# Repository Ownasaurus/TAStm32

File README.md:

# TAStm32
Please see the "Projects" section for an overview of the current status of this project!

Please see the "Wiki" section for the technical details of the serial communication protocol!

### Overview

This project aims to create an easy-to-use, multi-system TAS replay device to be used on actual consoles. The name of this project comes from the fact that it is powered by a STM32F4 microcontroller.

## How to use this device

#### Get Python3!
Install the [latest Python 3 release](https://www.python.org/downloads/)

(You may need to log out/log in to refresh the PATH variable)

Then install the required python modules with the following command:

    python3 -m pip install -r python/requirements.txt
    
#### Linux users -- make sure you are in the dialout and plugdev groups!

### Get the python scripts

Download the latest python scripts from https://github.com/Ownasaurus/TAStm32/releases/download/latest/python.zip

### Usage

Dumped TAS movies are available in the [TASBot projects repo](https://github.com/dwangoac/TASBot-Projects/tree/master/replayfiles)

[Scripts to dump your own TASes](https://github.com/dwangoac/TASBot-Projects/blob/master/Dump_Scripts/)

Once you've prepared a movie dump, use it with the TAStm32. Here is one example example is here:

    python3 tastm32.py --console snes --players 1,5 --dpcm --clock 14 --transition 2123 A --blank 1 smb3_agdq.r16m
    
Another option is to use python to run main.py, allowing you to utilize a GUI crated by Zayitskin. You can find more information on his repo here: https://github.com/Zayitskin/TAStm32GUI

## Upgrading firmware 

If it's the first time you're flashing it, short the "DFU" Pins (J13) while plugging tastm32 in.

#### Linux
    apt install dfu-util
OR the equivalent in your distribution. Then run:

    make v3 && make flash

Or :

    make v4 && make flash

#### Windows
1. Install STM32CubeProgrammer
1. Run the tastm32-dfu.py script to put the device in DFU mode (or if it's the first time you're flashing it, short the "DFU" Pins (J13) while plugging tastm32's USB cable into your computer).
1. Use the STM32CubeProgrammer software to flash the latest firmware. The latest firmware can always be found here: https://github.com/Ownasaurus/TAStm32/releases/download/latest/tastm32v3.hex
or
https://github.com/Ownasaurus/TAStm32/releases/download/latest/tastm32v4.hex

## Development (advanced users)

Do you want to fork the codebase and make your own tweaks? Here is some information that may help you.

### Compilation

#### Linux
    apt install gcc-arm-none-eabi binutils-arm-none-eabi libnewlib-arm-none-eabi
OR the equivalent in your distribution. Then run:

    make v3
    
Or : 

    make v4
    
Depending on if you have a v3 or v4 board. (v4 boards were released after July 2021)

#### Windows
1. Install Atollic TrueStudio
1. Right-click on the project > Build Configurations > Set Active, then click "Release v3" or "Release v4" depending on your board version. (v4s came out around July 2021)
1. Project > Build Project and check that the console shows no errors. The last line before "build finished" should be "arm-atollic-eabi-objcopy -O ihex TAStm32.elf TAStm32.hex".
1. Feel free to use the helper scripts "setenv.bat" and either "flashv3.bat" or "flashv4.bat" to assist in flashing firmware. These scripts will work if you have compiled using TrueStudio and if you have STM32CubeProgrammer installed.

### Special Thanks
#### rasteri (@rasteri) - Standalone USB playback, SNES multitap, v4 PCB, and more!
#### TheMas3212 (@TheMas3212) - Aided with all things python, designing the serial communication protocol, helping with PCB design, and debugging throughout the whole process.
#### total (@tewtal) - Helped with NES/SNES protocol and debugging. Provided his code as a reference
#### booto (@booto) - Helped fix N64/GC protocols, serial-over-USB, and debugging
#### Skippy - Pretty much helped a little bit with everything: including software, hardware, advice on proper tools, and more!

dwangoAC (@dwangoac) - warmly accepting me into the TASBot community

micro500 (@micro500) - spent a lot of time teaching me how console replay devices work at a low level

true - for teaching me hardware concepts, helping me choose the perfect MCU for the job, and explaining a lot of low-level things to me

Tien Majerle (@MaJerle) - the owner of https://stm32f4-discovery.net/ helped me with the function which jumps to the DFU bootloader code

CraftedCart - Designed the awesome-looking 3D case

Ilari - for being an extraordinary wealth of knowledge on most topics

Serisium (@serisium) - helped with debugging and PCB design

rcombs (@rcombs) - helped with optimizing the N64 protocol

Sauraen (@sauraen) - Linux setup and installation notes, multiplayer GC/N64 support, misc. GC/N64 improvements

Derf - worked on debugging the genesis protocol together

sspx (@SuperSpyTX) - For help with finding a bug in the N64 controller identity code.

#### If I accidentally forgot to credit you, please let me know so I can fix it!

 - Ownasaurus

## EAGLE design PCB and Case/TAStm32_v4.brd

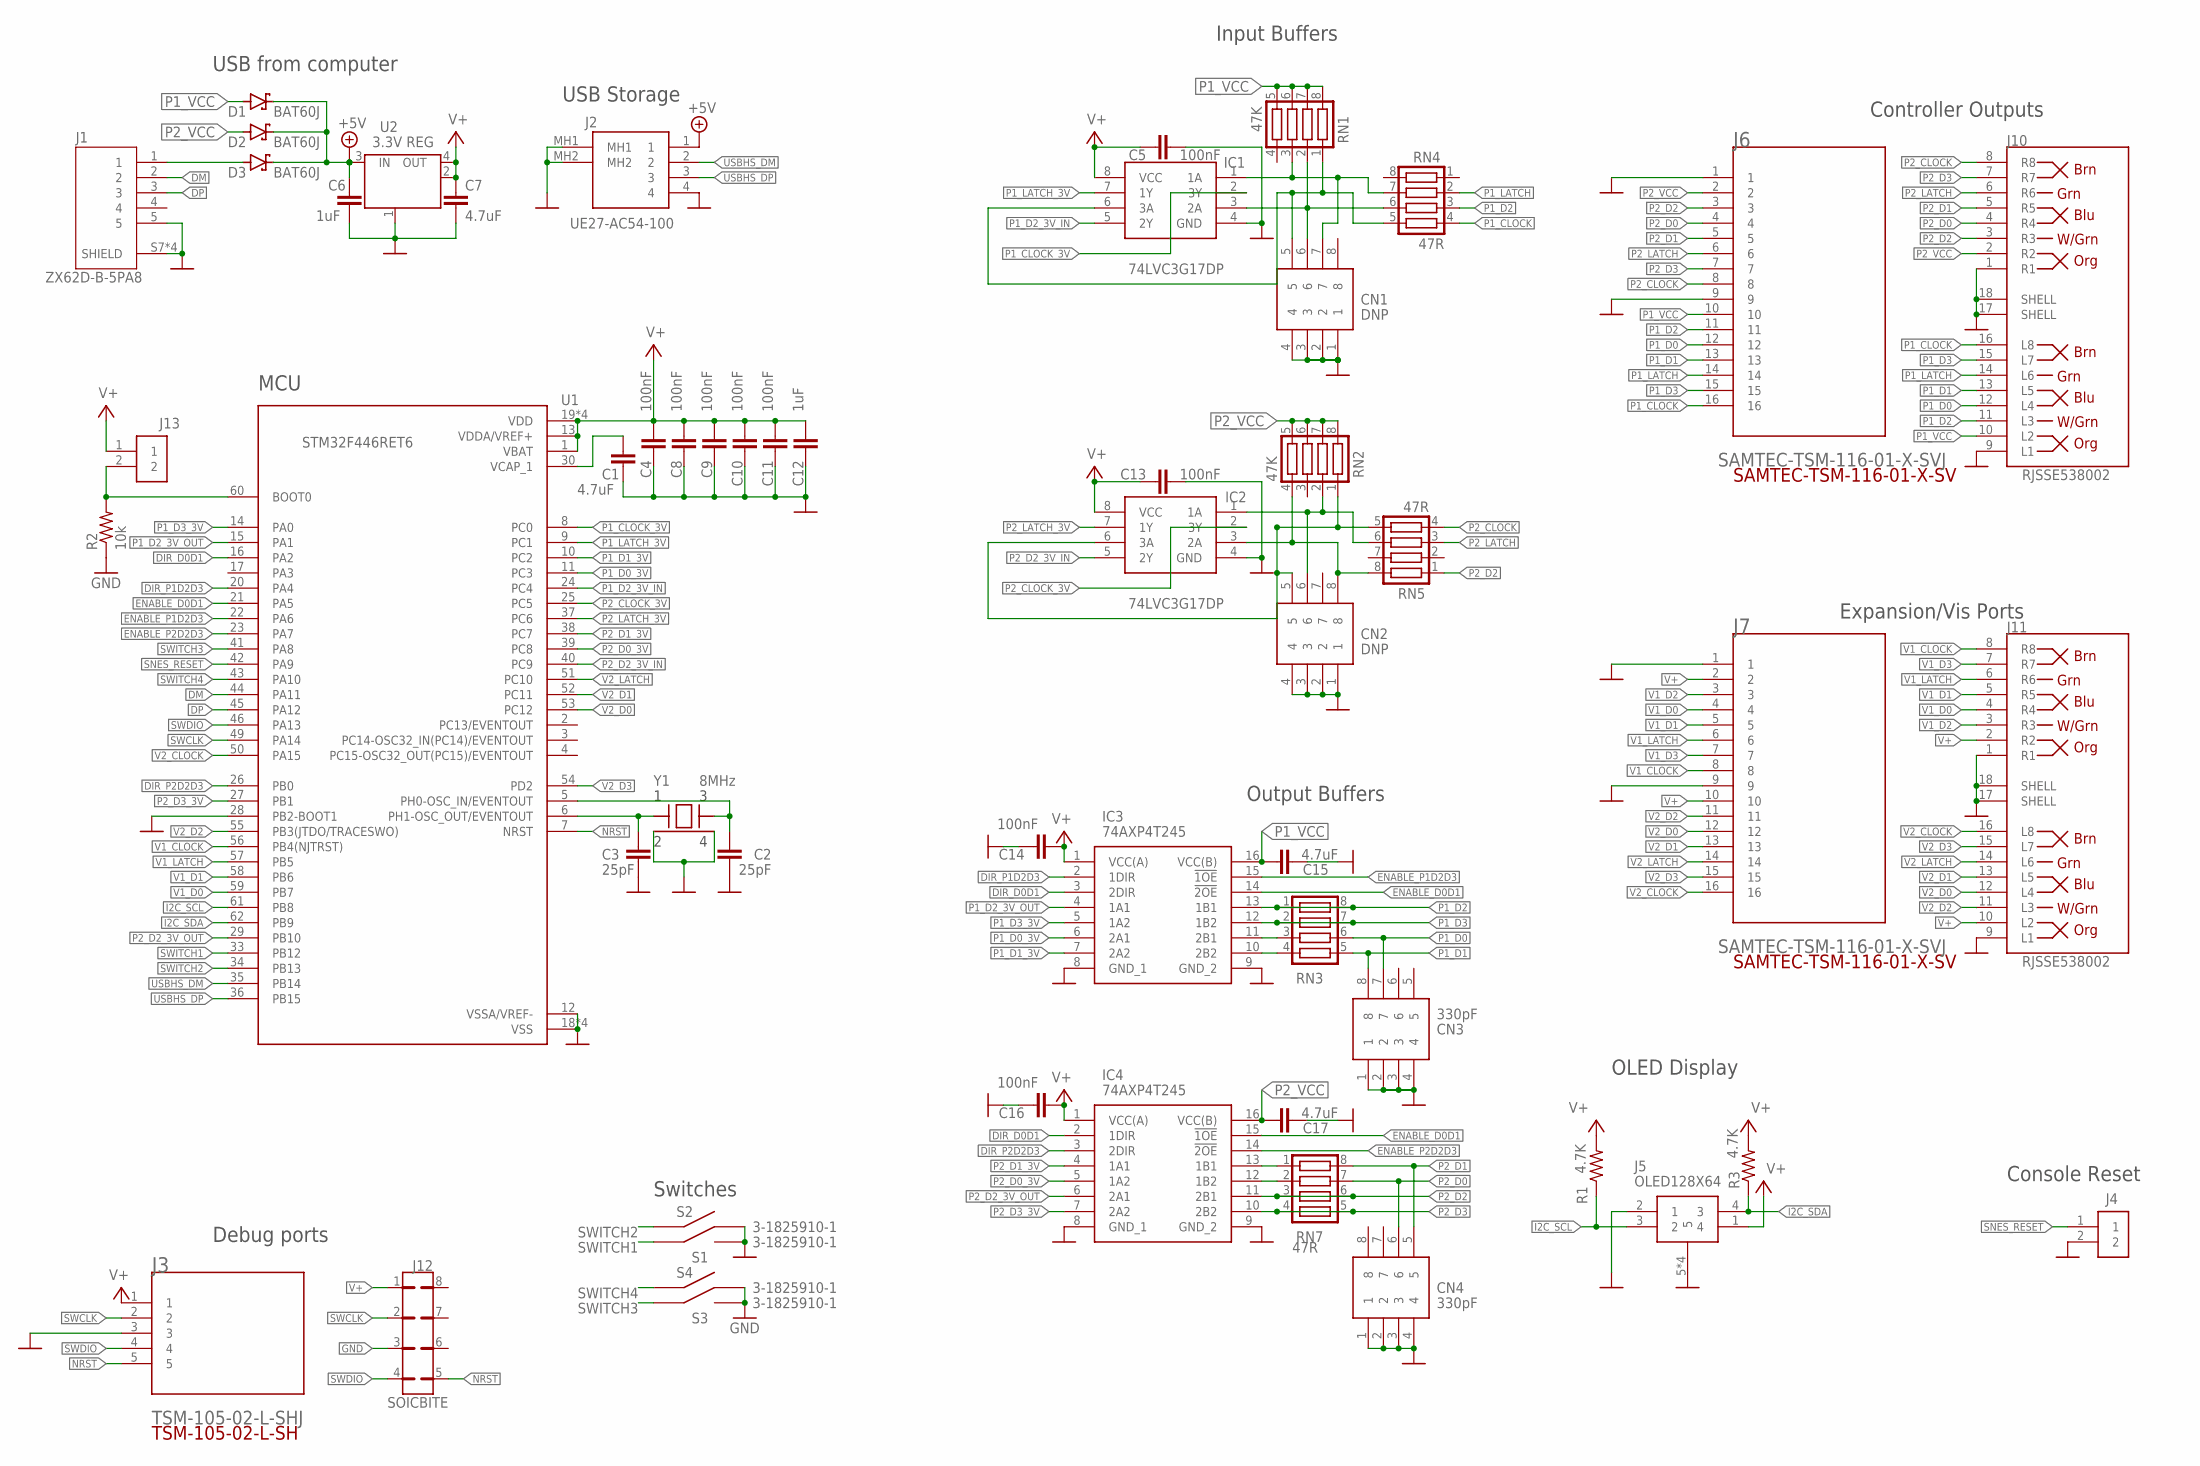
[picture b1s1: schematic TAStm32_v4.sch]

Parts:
C1, C7, C15, C17: 4.7uF; C0603K
C2, C3: 25pF; C0603K
C4, C5, C8, C9, C10, C11, C13, C14, C16: 100nF; C0603K
C6, C12: 1uF; C0603K
CN1, CN2: DNP; CA0612KRX7R7BB104
CN3, CN4: 330pF; CA0612KRX7R7BB104
D1, D2, D3: BAT60J; DIODE_SOD323_ST
IC1, IC2: 74LVC3G17DP; SOP65P400X110-8N
IC3, IC4: 74AXP4T245; SOP65P640X110-16N
J1: ZX62D-B-5PA8; HIROSE_ZX62D-B-5PA8
J2: UE27-AC54-100; UE27AC54100
J3: TSM-105-02-L-SHJ; TSM-105-02-L-SH
J4, J13: CONSOLE_RESET; SAMTEC-TSM-102-01-X-SH
J5: OLED128X64; OLED
J6, J7: SAMTEC-TSM-116-01-X-SVJ; SAMTEC-TSM-116-01-X-SV
J10, J11: RJSSE538002; AMPHENOL_RJSSE538002
J12: SOICBITE
R1, R3: 4.7K; R0805
R2: 10k; R0805
RN1, RN2: 47K; CTS742C083
RN3: CTS742C083
RN4, RN5, RN7: 47R; CTS742C083
S1, S2, S3, S4: 3-1825910-1; 3-1825910-1_318259101
U1: STM32F446RET6; QFP50P1200X1200X160-64N
U2: 3.3V REG; SOT223
Y1: 8MHz; DFN-4

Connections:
+5V: C6.2, D1.C, D2.C, D3.C, J2.1, U2.3 (IN)
BOOT0: J13.2, R2.2, U1.60 (BOOT0)
DIR_D0D1: IC3.3 (2DIR), IC4.2 (1DIR), U1.16 (PA2)
DIR_P1D2D3: IC3.2 (1DIR), U1.20 (PA4)
DIR_P2D2D3: IC4.3 (2DIR), U1.26 (PB0)
DM: J1.2, U1.44 (PA11)
DP: J1.3, U1.45 (PA12)
ENABLE_D0D1: IC3.14 (!2OE), IC4.15 (!1OE), U1.21 (PA5)
ENABLE_P1D2D3: IC3.15 (!1OE), U1.22 (PA6)
ENABLE_P2D2D3: IC4.14 (!2OE), U1.23 (PA7)
GND: C1.2, C2.1, C3.1, C4.1, C5.2, C6.1, C7.1, C8.1, C9.1, C10.1, C11.1, C12.1, C13.2, C14.1, C15.2, C16.1, C17.2, CN1.1, CN1.2, CN1.3, CN1.4, CN2.1, CN2.2, CN2.3, CN2.4, CN3.1, CN3.2, CN3.3, CN3.4, CN4.1, CN4.2, CN4.3, CN4.4, IC1.4 (GND), IC2.4 (GND), IC3.8 (GND_1), IC3.9 (GND_2), IC4.8 (GND_1), IC4.9 (GND_2), J1.5, J1.S7 (SHIELD), J1.S8 (SHIELD), J1.S9 (SHIELD), J1.S10 (SHIELD), J2.4, J2.MH1, J2.MH2, J3.3, J4.2, J5.2 (1), J5.5, J5.6 (5), J5.7 (5), J5.8 (5), J6.1, J6.9, J7.1, J7.9, J10.1 (R1), J10.9 (L1), J10.17 (SHELL), J10.18 (SHELL), J11.1 (R1), J11.9 (L1), J11.17 (SHELL), J11.18 (SHELL), J12.3, R2.1, S1.3, S1.4, S2.3, S2.4, S3.3, S3.4, S4.3, S4.4, U1.12 (VSSA/VREF-), U1.18 (VSS), U1.28 (PB2-BOOT1), U1.31 (VSS)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
I2C_SCL: J5.3 (2), R1.1, U1.61 (PB8)
I2C_SDA: J5.4 (3), R3.1, U1.62 (PB9)
unnamed: D3.A, J1.1
unnamed: CN2.6, IC2.1 (1A), RN2.2, RN5.6
unnamed: C3.2, U1.6 (PH1-OSC_OUT/EVENTOUT), Y1.1
unnamed: CN2.5, IC2.6 (3A), RN2.1, RN5.5
unnamed: CN2.8, IC2.3 (2A), RN2.4, RN5.8
unnamed: IC3.11 (2B1), RN3.3
unnamed: IC3.10 (2B2), RN3.4
unnamed: IC4.12 (1B2), RN7.2
unnamed: IC4.13 (1B1), RN7.1
unnamed: CN1.7, IC1.1 (1A), RN1.3, RN4.7
unnamed: CN1.5, IC1.6 (3A), RN1.1, RN4.5
unnamed: CN1.6, IC1.3 (2A), RN1.2, RN4.6
NRST: J3.5, J12.5, U1.7 (NRST)
P1_CLOCK: J6.16, J10.16 (L8), RN4.4
P1_CLOCK_3V: IC1.2 (3Y), U1.8 (PC0)
P1_D0: CN3.7, J6.12, J10.12 (L4), RN3.6
P1_D0_3V: IC3.6 (2A1), U1.11 (PC3)
P1_D1: CN3.8, J6.13, J10.13 (L5), RN3.5
P1_D1_3V: IC3.7 (2A2), U1.10 (PC2)
P1_D2: IC3.13 (1B1), J6.11, J10.11 (L3), RN3.1, RN3.8, RN4.3
P1_D2_3V_IN: IC1.5 (2Y), U1.24 (PC4)
P1_D2_3V_OUT: IC3.4 (1A1), U1.15 (PA1)
P1_D3: IC3.12 (1B2), J6.15, J10.15 (L7), RN3.2, RN3.7
P1_D3_3V: IC3.5 (1A2), U1.14 (PA0)
P1_LATCH: J6.14, J10.14 (L6), RN4.2
P1_LATCH_3V: IC1.7 (1Y), U1.9 (PC1)
P1_VCC: C15.1, D1.A, IC3.16 (VCC(B)), J6.10, J10.10 (L2), RN1.5, RN1.6, RN1.7, RN1.8
P2_CLOCK: J6.8, J10.8 (R8), RN5.4
P2_CLOCK_3V: IC2.2 (3Y), U1.25 (PC5)
P2_D0: CN4.6, J6.4, J10.4 (R4), RN7.7
P2_D0_3V: IC4.5 (1A2), U1.39 (PC8)
P2_D1: CN4.5, J6.5, J10.5 (R5), RN7.8
P2_D1_3V: IC4.4 (1A1), U1.38 (PC7)
P2_D2: IC4.11 (2B1), J6.3, J10.3 (R3), RN5.1, RN7.3, RN7.6
P2_D2_3V_IN: IC2.5 (2Y), U1.40 (PC9)
P2_D2_3V_OUT: IC4.6 (2A1), U1.29 (PB10)
P2_D3: IC4.10 (2B2), J6.7, J10.7 (R7), RN7.4, RN7.5
P2_D3_3V: IC4.7 (2A2), U1.27 (PB1)
P2_LATCH: J6.6, J10.6 (R6), RN5.3
P2_LATCH_3V: IC2.7 (1Y), U1.37 (PC6)
P2_VCC: C17.1, D2.A, IC4.16 (VCC(B)), J6.2, J10.2 (R2), RN2.5, RN2.6, RN2.7, RN2.8
SNES_RESET: J4.1, U1.42 (PA9)
SWCLK: J3.2, J12.2, U1.49 (PA14)
SWDIO: J3.4, J12.4, U1.46 (PA13)
SWITCH1: S1.1, S1.2, U1.33 (PB12)
SWITCH2: S2.1, S2.2, U1.34 (PB13)
SWITCH3: S3.1, S3.2, U1.41 (PA8)
SWITCH4: S4.1, S4.2, U1.43 (PA10)
USBHS_DM: J2.2, U1.35 (PB14)
USBHS_DP: J2.3, U1.36 (PB15)
V1_CLOCK: J7.8, J11.8 (R8), U1.56 (PB4(NJTRST))
V1_D0: J7.4, J11.4 (R4), U1.59 (PB7)
V1_D1: J7.5, J11.5 (R5), U1.58 (PB6)
V1_D2: J7.3, J11.3 (R3)
V1_D3: J7.7, J11.7 (R7)
V1_LATCH: J7.6, J11.6 (R6), U1.57 (PB5)
V2_CLOCK: J7.16, J11.16 (L8), U1.50 (PA15)
V2_D0: J7.12, J11.12 (L4), U1.53 (PC12)
V2_D1: J7.13, J11.13 (L5), U1.52 (PC11)
V2_D2: J7.11, J11.11 (L3), U1.55 (PB3(JTDO/TRACESWO))
V2_D3: J7.15, J11.15 (L7), U1.54 (PD2)
V2_LATCH: J7.14, J11.14 (L6), U1.51 (PC10)
V+: C4.2, C5.1, C7.2, C8.2, C9.2, C10.2, C11.2, C12.2, C13.1, C14.2, C16.2, IC1.8 (VCC), IC2.8 (VCC), IC3.1 (VCC(A)), IC4.1 (VCC(A)), J3.1, J5.1 (4), J7.2, J7.10, J11.2 (R2), J11.10 (L2), J12.1, J13.1, R1.2, R3.2, U1.1 (VBAT), U1.13 (VDDA/VREF+), U1.19 (VDD), U1.32 (VDD), U1.48 (VDD), U1.64 (VDD), U2.2 (OUT), U2.4 (OUT)
VCAP: C1.1, U1.30 (VCAP_1)
XTAL1: C2.2, U1.5 (PH0-OSC_IN/EVENTOUT), Y1.3

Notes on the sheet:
USB from computer
USB Storage
MCU
Debug ports
OLED Display
Console Reset
Controller Outputs
Expansion/Vis Ports
Input Buffers
Output Buffers
Switches

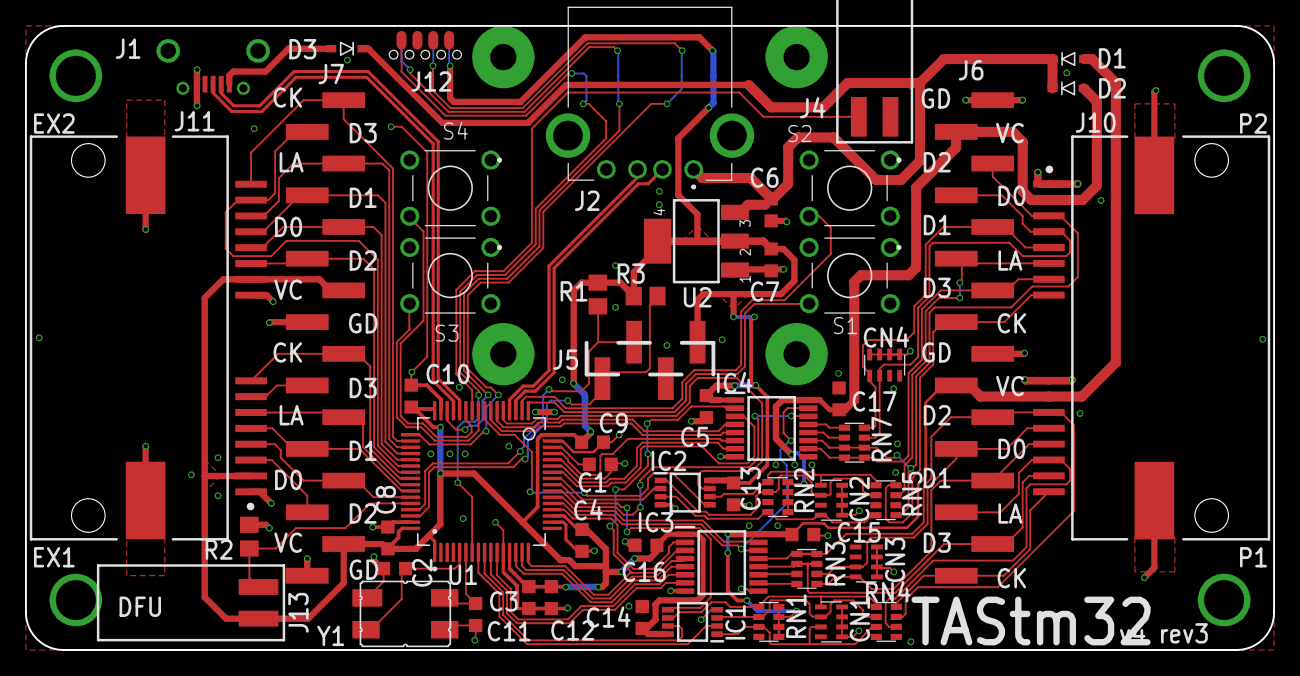
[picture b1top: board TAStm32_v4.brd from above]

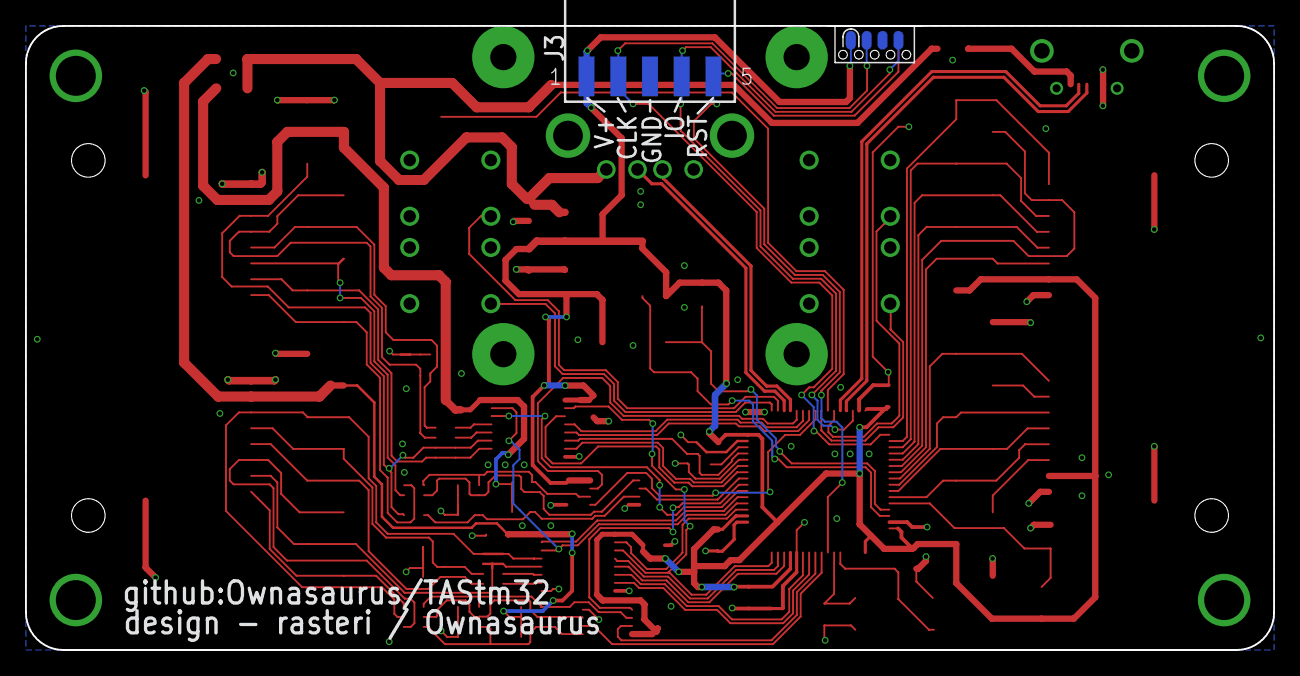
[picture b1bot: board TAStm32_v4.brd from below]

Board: 2 copper layers, 100.0 x 50.0 mm, 55 parts (2 on the bottom side), 78 nets.

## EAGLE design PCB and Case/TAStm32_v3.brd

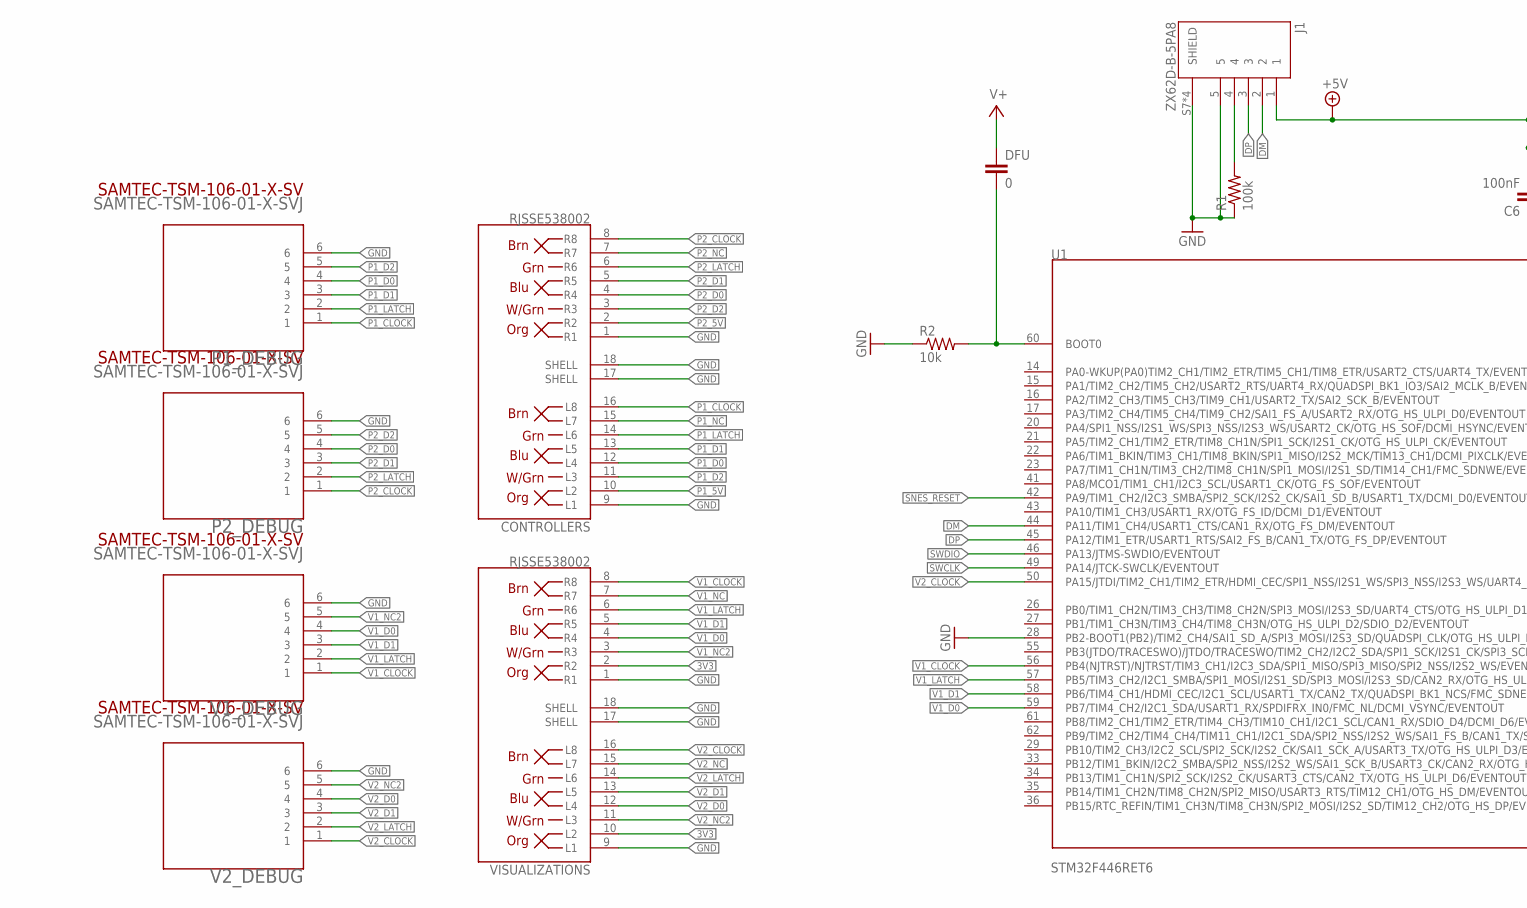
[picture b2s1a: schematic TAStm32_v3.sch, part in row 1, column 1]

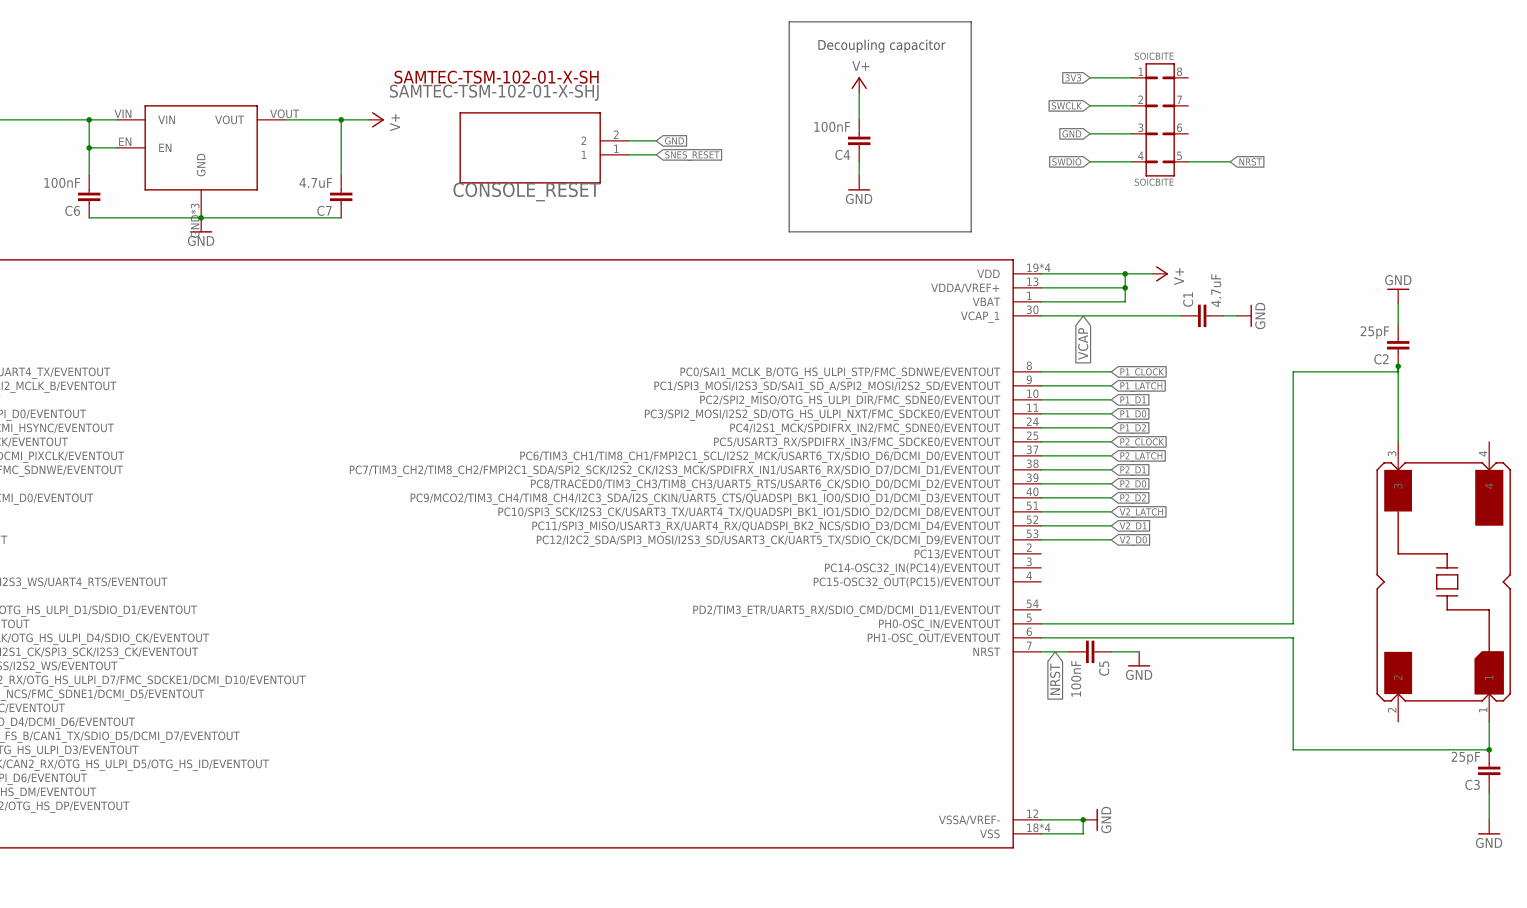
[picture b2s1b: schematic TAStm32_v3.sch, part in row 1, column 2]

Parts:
C1, C7: 4.7uF; C0805K
C2, C3: 25pF; C0805K
C4, C5, C6: 100nF; C0805K
CONSOLE_RESET: SAMTEC-TSM-102-01-X-SHJ; SAMTEC-TSM-102-01-X-SH
CONTROLLERS: RJSSE538002; AMPHENOL_RJSSE538002
DFU: 0; C0603
J1: ZX62D-B-5PA8; HIROSE_ZX62D-B-5PA8
P1_DEBUG, P2_DEBUG: SAMTEC-TSM-106-01-X-SVJ; SAMTEC-TSM-106-01-X-SV
R1: 100k; R0805
R2: 10k; R0805
SOICBITE: SOICBITE
U1: STM32F446RET6; QFP50P1200X1200X160-64N
V1_DEBUG, V2_DEBUG: SAMTEC-TSM-106-01-X-SVJ; SAMTEC-TSM-106-01-X-SV
VISUALIZATIONS: RJSSE538002; AMPHENOL_RJSSE538002
V_REG: S-1172B33-U5T1G
XTAL: ABMM-8.000MHZ-B2-T; DFN-4

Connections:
3V3: C4.2, C7.2, DFU.1, SOICBITE.1, U1.1 (VBAT), U1.13 (VDDA/VREF+), U1.19 (VDD), U1.32 (VDD), U1.48 (VDD), U1.64 (VDD), VISUALIZATIONS.2 (R2), VISUALIZATIONS.10 (L2), V_REG.VOUT
+5V: C6.2, J1.1, V_REG.EN, V_REG.VIN
BOOT0: DFU.2, R2.2, U1.60 (BOOT0)
DM: J1.2, U1.44 (PA11/TIM1_CH4/USART1_CTS/CAN1_RX/OTG_FS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)
DP: J1.3, U1.45 (PA12/TIM1_ETR/USART1_RTS/SAI2_FS_B/CAN1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)
GND: C1.2, C2.2, C3.1, C4.1, C5.1, C6.1, C7.1, CONSOLE_RESET.2, CONTROLLERS.1 (R1), CONTROLLERS.9 (L1), CONTROLLERS.17 (SHELL), CONTROLLERS.18 (SHELL), J1.5, J1.S7 (SHIELD), J1.S8 (SHIELD), J1.S9 (SHIELD), J1.S10 (SHIELD), P1_DEBUG.6, P2_DEBUG.6, R1.1, R2.1, SOICBITE.3, U1.12 (VSSA/VREF-), U1.18 (VSS), U1.28 (PB2-BOOT1(PB2)/TIM2_CH4/SAI1_SD_A/SPI3_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), U1.31 (VSS), U1.47 (VSS), U1.63 (VSS), V1_DEBUG.6, V2_DEBUG.6, VISUALIZATIONS.1 (R1), VISUALIZATIONS.9 (L1), VISUALIZATIONS.17 (SHELL), VISUALIZATIONS.18 (SHELL), V_REG.GND, V_REG.GND2 (GND), V_REG.GND3 (GND)
ID: J1.4, R1.2
NRST: C5.2, SOICBITE.5, U1.7 (NRST)
P1_5V: CONTROLLERS.10 (L2)
P1_CLOCK: CONTROLLERS.16 (L8), P1_DEBUG.1, U1.8 (PC0/SAI1_MCLK_B/OTG_HS_ULPI_STP/FMC_SDN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)
P1_D0: CONTROLLERS.12 (L4), P1_DEBUG.4, U1.11 (PC3/SPI2_MOSI/I2S2_SD/OTG_HS_ULPI_NXT/F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)
P1_D1: CONTROLLERS.13 (L5), P1_DEBUG.3, U1.10 (PC2/SPI2_MISO/OTG_HS_ULPI_DIR/FMC_SDNE0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)
P1_D2: CONTROLLERS.11 (L3), P1_DEBUG.5, U1.24 (PC4/I2S1_MCK/SPDIFRX_IN2/FMC_SDNE0/EVEN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)
P1_LATCH: CONTROLLERS.14 (L6), P1_DEBUG.2, U1.9 (PC1/SPI3_MOSI/I2S3_SD/SAI1_SD_A/SPI2_MO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)
P1_NC: CONTROLLERS.15 (L7)
P2_5V: CONTROLLERS.2 (R2)
P2_CLOCK: CONTROLLERS.8 (R8), P2_DEBUG.1, U1.25 (PC5/USART3_RX/SPDIFRX_IN3/FMC_SDCKE0/EV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)
P2_D0: CONTROLLERS.4 (R4), P2_DEBUG.4, U1.39 (PC8/TRACED0/TIM3_CH3/TIM8_CH3/UART5_RTS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)
P2_D1: CONTROLLERS.5 (R5), P2_DEBUG.3, U1.38 (PC7/TIM3_CH2/TIM8_CH2/FMPI2C1_SDA/SPI2_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)
P2_D2: CONTROLLERS.3 (R3), P2_DEBUG.5, U1.40 (PC9/MCO2/TIM3_CH4/TIM8_CH4/I2C3_SDA/I2S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)
P2_LATCH: CONTROLLERS.6 (R6), P2_DEBUG.2, U1.37 (PC6/TIM3_CH1/TIM8_CH1/FMPI2C1_SCL/I2S2_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)
P2_NC: CONTROLLERS.7 (R7)
SNES_RESET: CONSOLE_RESET.1, U1.42 (PA9/TIM1_CH2/I2C3_SMBA/SPI2_SCK/I2S2_CK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)
SWCLK: SOICBITE.2, U1.49 (PA14/JTCK-SWCLK/EVENTOUT)
SWDIO: SOICBITE.4, U1.46 (PA13/JTMS-SWDIO/EVENTOUT)
V1_CLOCK: U1.56 (PB4(NJTRST)/NJTRST/TIM3_CH1/I2C3_SDA/SP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), V1_DEBUG.1, VISUALIZATIONS.8 (R8)
V1_D0: U1.59 (PB7/TIM4_CH2/I2C1_SDA/USART1_RX/SPDIFRX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), V1_DEBUG.4, VISUALIZATIONS.4 (R4)
V1_D1: U1.58 (PB6/TIM4_CH1/HDMI_CEC/I2C1_SCL/USART1_T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), V1_DEBUG.3, VISUALIZATIONS.5 (R5)
V1_LATCH: U1.57 (PB5/TIM3_CH2/I2C1_SMBA/SPI1_MOSI/I2S1_S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), V1_DEBUG.2, VISUALIZATIONS.6 (R6)
V1_NC: VISUALIZATIONS.7 (R7)
V1_NC2: V1_DEBUG.5, VISUALIZATIONS.3 (R3)
V2_CLOCK: U1.50 (PA15/JTDI/TIM2_CH1/TIM2_ETR/HDMI_CEC/SP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), V2_DEBUG.1, VISUALIZATIONS.16 (L8)
V2_D0: U1.53 (PC12/I2C2_SDA/SPI3_MOSI/I2S3_SD/USART3_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), V2_DEBUG.4, VISUALIZATIONS.12 (L4)
V2_D1: U1.52 (PC11/SPI3_MISO/USART3_RX/UART4_RX/QUADS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), V2_DEBUG.3, VISUALIZATIONS.13 (L5)
V2_LATCH: U1.51 (PC10/SPI3_SCK/I2S3_CK/USART3_TX/UART4_T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), V2_DEBUG.2, VISUALIZATIONS.14 (L6)
V2_NC: VISUALIZATIONS.15 (L7)
V2_NC2: V2_DEBUG.5, VISUALIZATIONS.11 (L3)
VCAP: C1.1, U1.30 (VCAP_1)
XTAL1: C2.1, U1.5 (PH0-OSC_IN/EVENTOUT), XTAL.3
XTAL2: C3.2, U1.6 (PH1-OSC_OUT/EVENTOUT), XTAL.1

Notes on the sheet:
Decoupling capacitor

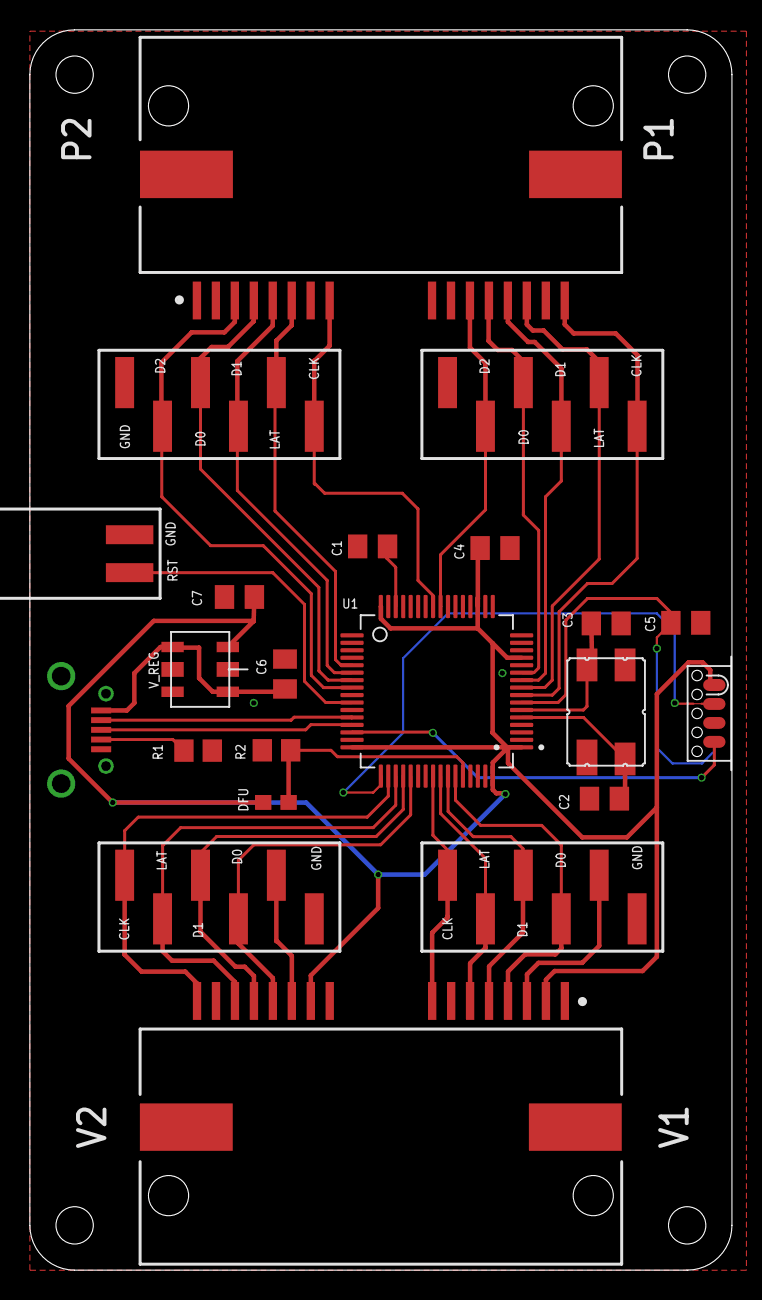
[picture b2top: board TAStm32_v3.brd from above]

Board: 2 copper layers, 47.0 x 83.1 mm, 22 parts (0 on the bottom side), 34 nets.

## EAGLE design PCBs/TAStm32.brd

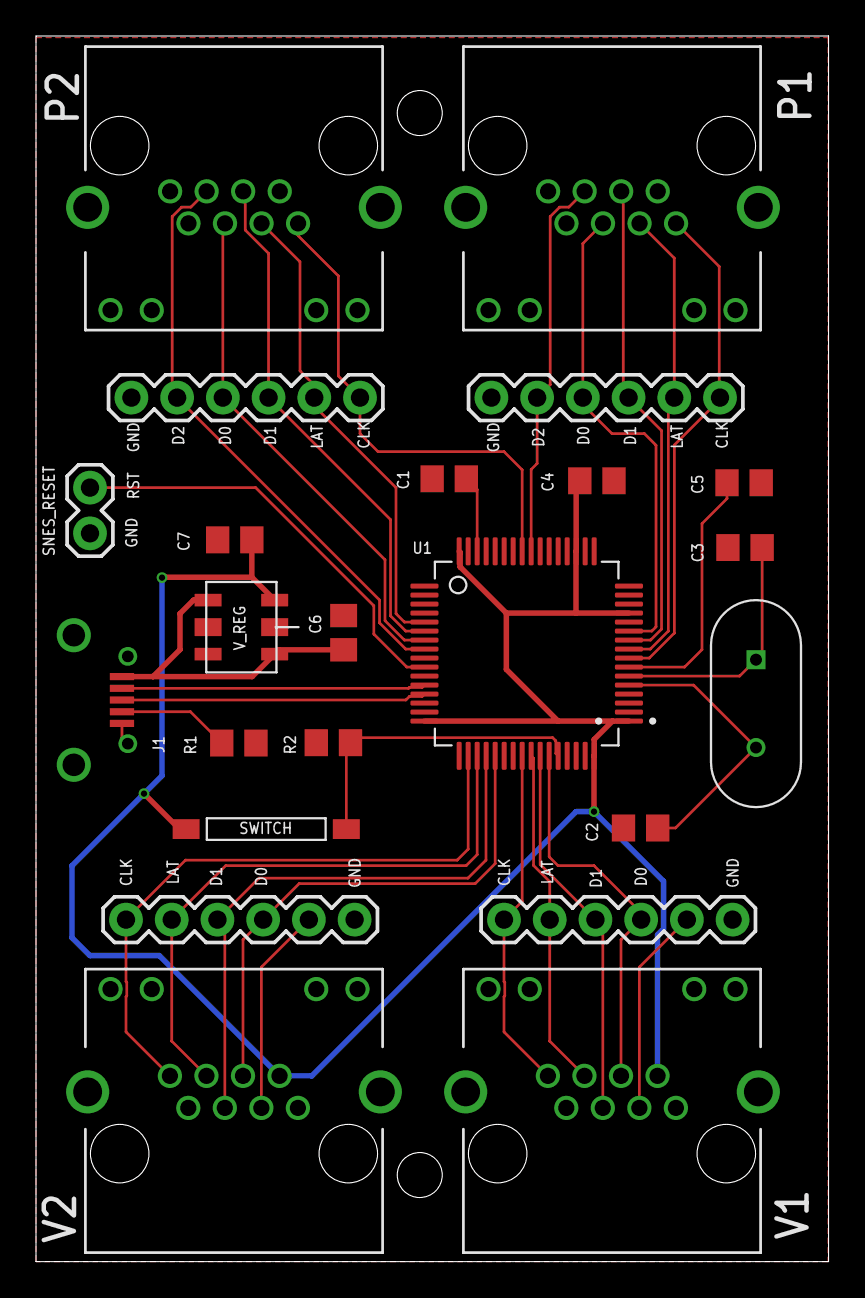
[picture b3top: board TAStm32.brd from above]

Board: 2 copper layers, 44.0 x 68.1 mm, 23 parts (0 on the bottom side), 32 nets.

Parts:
8MHZ_XTAL: XTAL_HC49; XTAL_HC49P488W45L1150T500H350
C1: 4.7uF; C0805
C2, C3: 25pF; C0805
C4, C5, C6, C7: 100nF; C0805
J1: ZX62D-B-5PA8; HIROSE_ZX62D-B-5PA8
P1, P2: RJHSE-5381; AMPHENOL_RJHSE-5381
P1_DEBUG, P2_DEBUG: 6_PIN_SERIAL_CABLEPTH; FTDI_BASIC
R1: 100k; R0805
R2: 10k; R0805
SNES_RESET: 1; 1X02
SWITCH: DM01
U1: STM32F446RET6; QFP50P1200X1200X160-64N
V1, V2: RJHSE-5381; AMPHENOL_RJHSE-5381
V1_DEBUG, V2_DEBUG: 6_PIN_SERIAL_CABLEPTH; FTDI_BASIC
V_REG: S-1172B33-U5T1G

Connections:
3V3: C4.2, C7.2, SWITCH.P$1, U1.1, U1.13, U1.19, U1.32, U1.48, U1.64, V1.2, V2.2, V_REG.VOUT
+5V: C6.2, J1.1, V_REG.EN, V_REG.VIN
DM: J1.2, U1.44
DP: J1.3, U1.45
GND: C1.2, C2.2, C3.1, C4.1, C5.1, C6.1, C7.1, J1.5, J1.S7, J1.S8, J1.S9, J1.S10, P1.1, P1.9, P1.11, P1_DEBUG.GND, P2.1, P2.9, P2.11, P2_DEBUG.GND, R1.1, R2.1, SNES_RESET.2, U1.12, U1.18, U1.28, U1.31, U1.47, U1.63, V1.1, V1_DEBUG.GND, V2.1, V2_DEBUG.GND, V_REG.GND, V_REG.GND2, V_REG.GND3
unnamed: R2.2, SWITCH.P$2, U1.60
unnamed: C5.2, U1.7
unnamed: C1.1, U1.30
unnamed: J1.4, R1.2
P1_CLOCK: P1.8, P1_DEBUG.DTR, U1.8
P1_D0: P1.4, P1_DEBUG.VCC, U1.11
P1_D1: P1.5, P1_DEBUG.TXO, U1.10
P1_D2: P1.3, P1_DEBUG.CTS, U1.24
P1_LATCH: P1.6, P1_DEBUG.RXI, U1.9
P2_CLOCK: P2.8, P2_DEBUG.DTR, U1.25
P2_D0: P2.4, P2_DEBUG.VCC, U1.39
P2_D1: P2.5, P2_DEBUG.TXO, U1.38
P2_D2: P2.3, P2_DEBUG.CTS, U1.40
P2_LATCH: P2.6, P2_DEBUG.RXI, U1.37
SNES_RESET: SNES_RESET.1, U1.42
V1_CLOCK: U1.56, V1.8, V1_DEBUG.DTR
V1_D0: U1.59, V1.4, V1_DEBUG.VCC
V1_D1: U1.58, V1.5, V1_DEBUG.TXO
V1_LATCH: U1.57, V1.6, V1_DEBUG.RXI
V1_NC2: V1.3, V1_DEBUG.CTS
V2_CLOCK: U1.50, V2.8, V2_DEBUG.DTR
V2_D0: U1.53, V2.4, V2_DEBUG.VCC
V2_D1: U1.52, V2.5, V2_DEBUG.TXO
V2_LATCH: U1.51, V2.6, V2_DEBUG.RXI
V2_NC2: V2.3, V2_DEBUG.CTS
XTAL1: 8MHZ_XTAL.2, C2.1, U1.5
XTAL2: 8MHZ_XTAL.1, C3.2, U1.6

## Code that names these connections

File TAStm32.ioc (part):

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Mcu.Name=STM32F446R(C-E)Tx
Mcu.Package=LQFP64
Mcu.UserName=STM32F446RETx
PA0-WKUP.GPIOParameters=GPIO_Speed,GPIO_Label
PA0-WKUP.GPIO_Label=P1_DATA_3
PA0-WKUP.GPIO_Speed=GPIO_SPEED_FREQ_MEDIUM
PA0-WKUP.Signal=GPIO_Output
PA1.GPIOParameters=GPIO_PuPd,GPIO_Label
PA1.GPIO_Label=P1_DATA_2_OUT
PA1.GPIO_PuPd=GPIO_PULLUP
PA1.Signal=GPIO_Input
PA10.GPIOParameters=GPIO_Label
PA10.GPIO_Label=PA10
PA10.Signal=GPIO_Input
PA11.Mode=Device_Only
PA11.Signal=USB_OTG_FS_DM
PA12.Mode=Device_Only
PA12.Signal=USB_OTG_FS_DP
PA13.GPIOParameters=GPIO_Label
PA13.GPIO_Label=TMS
PA13.Mode=Serial_Wire
PA13.Signal=SYS_JTMS-SWDIO
PA14.GPIOParameters=GPIO_Label
PA14.GPIO_Label=TCK
PA14.Mode=Serial_Wire
PA14.Signal=SYS_JTCK-SWCLK
PA15.GPIOParameters=GPIO_Speed,PinState,GPIO_Label
PA15.GPIO_Label=V2_CLOCK
PA15.GPIO_Speed=GPIO_SPEED_FREQ_VERY_HIGH
PA15.PinState=GPIO_PIN_RESET
PA15.Signal=GPIO_Output
PA2.GPIOParameters=GPIO_Speed,PinState,GPIO_Label
PA2.GPIO_Label=DIR_D0D1
PA2.GPIO_Speed=GPIO_SPEED_FREQ_MEDIUM
PA2.PinState=GPIO_PIN_SET
PA2.Signal=GPIO_Output
PA3.GPIOParameters=GPIO_PuPd,GPIO_Label
PA3.GPIO_Label=PA3
PA3.GPIO_PuPd=GPIO_PULLUP
PA3.Signal=GPIO_Input
PA4.GPIOParameters=GPIO_Speed,PinState,GPIO_Label
PA4.GPIO_Label=DIR_P1D2D3
PA4.GPIO_Speed=GPIO_SPEED_FREQ_MEDIUM
PA4.PinState=GPIO_PIN_SET
PA4.Signal=GPIO_Output
PA5.GPIOParameters=GPIO_Speed,PinState,GPIO_Label
PA5.GPIO_Label=ENABLE_D0D1
PA5.GPIO_Speed=GPIO_SPEED_FREQ_MEDIUM
PA5.PinState=GPIO_PIN_SET
PA5.Signal=GPIO_Output
PA6.GPIOParameters=GPIO_Speed,PinState,GPIO_Label
PA6.GPIO_Label=ENABLE_P1D2D3
PA6.GPIO_Speed=GPIO_SPEED_FREQ_MEDIUM
PA6.PinState=GPIO_PIN_SET
PA6.Signal=GPIO_Output
PA7.GPIOParameters=GPIO_Speed,PinState,GPIO_Label
PA7.GPIO_Label=ENABLE_P2D2D3
PA7.GPIO_Speed=GPIO_SPEED_FREQ_MEDIUM
PA7.PinState=GPIO_PIN_SET
PA7.Signal=GPIO_Output
PA8.GPIOParameters=GPIO_PuPd,GPIO_Label
PA8.GPIO_Label=PA8
PA8.GPIO_PuPd=GPIO_PULLUP
PA8.Signal=GPIO_Input
PA9.GPIOParameters=GPIO_Speed,GPIO_Label
PA9.GPIO_Label=SNES_RESET
PA9.GPIO_Speed=GPIO_SPEED_FREQ_MEDIUM
PA9.Signal=GPIO_Output
PB0.GPIOParameters=GPIO_Speed,GPIO_Label
PB0.GPIO_Label=DIR_P2D2D3
PB0.GPIO_Speed=GPIO_SPEED_FREQ_MEDIUM
PB0.Signal=GPIO_Output
PB1.GPIOParameters=GPIO_Label
PB1.GPIO_Label=P2_DATA_3
PB1.Signal=GPIO_Output
PB10.GPIOParameters=GPIO_Speed,GPIO_Label
PB10.GPIO_Label=P2_DATA_2_OUT
PB10.GPIO_Speed=GPIO_SPEED_FREQ_MEDIUM
PB10.Signal=GPIO_Output
PB12.GPIOParameters=GPIO_PuPd,GPIO_Label
PB12.GPIO_Label=PB12
PB12.GPIO_PuPd=GPIO_PULLUP
PB12.Signal=GPIO_Input
PB13.GPIOParameters=GPIO_PuPd,GPIO_Label
PB13.GPIO_Label=PB13
PB13.GPIO_PuPd=GPIO_PULLUP
PB13.Signal=GPIO_Input
PB14.Mode=Host_FS
PB14.Signal=USB_OTG_HS_DM
PB15.Mode=Host_FS
PB15.Signal=USB_OTG_HS_DP
PB3.GPIOParameters=GPIO_Label
PB3.GPIO_Label=V1_DATA_2
PB3.Signal=GPIO_Output
PB4.GPIOParameters=GPIO_Speed,PinState,GPIO_Label
PB4.GPIO_Label=V1_CLOCK
PB4.GPIO_Speed=GPIO_SPEED_FREQ_VERY_HIGH
PB4.PinState=GPIO_PIN_RESET
PB4.Signal=GPIO_Output
PB5.GPIOParameters=GPIO_Speed,GPIO_Label
PB5.GPIO_Label=V1_LATCH
PB5.GPIO_Speed=GPIO_SPEED_FREQ_VERY_HIGH
PB5.Signal=GPIO_Output
PB6.GPIOParameters=GPIO_Speed,PinState,GPIO_Label
PB6.GPIO_Label=V1_DATA_1
PB6.GPIO_Speed=GPIO_SPEED_FREQ_VERY_HIGH
PB6.PinState=GPIO_PIN_RESET
PB6.Signal=GPIO_Output
PB7.GPIOParameters=GPIO_Speed,PinState,GPIO_Label
PB7.GPIO_Label=V1_DATA_0
PB7.GPIO_Speed=GPIO_SPEED_FREQ_VERY_HIGH
PB7.PinState=GPIO_PIN_RESET
PB7.Signal=GPIO_Output
PB8.Mode=I2C
PB8.Signal=I2C1_SCL
PB9.Mode=I2C
PB9.Signal=I2C1_SDA
PC0.GPIOParameters=GPIO_PuPd,GPIO_Label
PC0.GPIO_Label=P1_CLOCK
PC0.GPIO_PuPd=GPIO_PULLDOWN
PC0.Signal=GPXTI0
PC1.GPIOParameters=GPIO_PuPd,GPIO_Label
PC1.GPIO_Label=P1_LATCH
PC1.GPIO_PuPd=GPIO_PULLDOWN
PC1.Signal=GPXTI1
PC10.GPIOParameters=GPIO_Speed,PinState,GPIO_Label
PC10.GPIO_Label=V2_LATCH
PC10.GPIO_Speed=GPIO_SPEED_FREQ_VERY_HIGH
PC10.PinState=GPIO_PIN_RESET
PC10.Signal=GPIO_Output
PC11.GPIOParameters=GPIO_Speed,PinState,GPIO_Label
PC11.GPIO_Label=V2_DATA_1
PC11.GPIO_Speed=GPIO_SPEED_FREQ_VERY_HIGH
PC11.PinState=GPIO_PIN_RESET
PC11.Signal=GPIO_Output
PC12.GPIOParameters=GPIO_Speed,PinState,GPIO_Label
PC12.GPIO_Label=V2_DATA_0
PC12.GPIO_Speed=GPIO_SPEED_FREQ_VERY_HIGH
PC12.PinState=GPIO_PIN_RESET
PC12.Signal=GPIO_Output
PC13.GPIOParameters=GPIO_PuPd,GPIO_Label
PC13.GPIO_Label=PC13
PC13.GPIO_PuPd=GPIO_PULLUP
PC13.Signal=GPIO_Input
PC14-OSC32_IN.GPIOParameters=GPIO_PuPd,GPIO_Label
PC14-OSC32_IN.GPIO_Label=PC14
PC14-OSC32_IN.GPIO_PuPd=GPIO_PULLUP
PC14-OSC32_IN.Signal=GPIO_Input
PC15-OSC32_OUT.GPIOParameters=GPIO_Label
PC15-OSC32_OUT.GPIO_Label=PC15
PC15-OSC32_OUT.Signal=GPIO_Output
PC2.GPIOParameters=GPIO_PuPd,GPIO_Label
PC2.GPIO_Label=P1_DATA_1
PC2.GPIO_PuPd=GPIO_PULLDOWN
PC2.Signal=GPIO_Input
PC3.GPIOParameters=GPIO_PuPd,GPIO_Label
PC3.GPIO_Label=P1_DATA_0
PC3.GPIO_PuPd=GPIO_PULLDOWN
PC3.Signal=GPIO_Input
PC4.GPIOParameters=GPIO_PuPd,GPIO_Label,GPIO_ModeDefaultEXTI
PC4.GPIO_Label=P1_DATA_2
PC4.GPIO_ModeDefaultEXTI=GPIO_MODE_IT_FALLING
PC4.GPIO_PuPd=GPIO_PULLDOWN
PC4.Signal=GPXTI4
PC5.GPIOParameters=GPIO_PuPd,GPIO_Label
PC5.GPIO_Label=P2_CLOCK
PC5.GPIO_PuPd=GPIO_PULLDOWN
PC5.Signal=GPXTI5
PC6.GPIOParameters=GPIO_PuPd,GPIO_Label
PC6.GPIO_Label=P2_LATCH
PC6.GPIO_PuPd=GPIO_PULLDOWN
PC6.Signal=GPIO_Input
PC7.GPIOParameters=GPIO_PuPd,GPIO_Label
PC7.GPIO_Label=P2_DATA_1
PC7.GPIO_PuPd=GPIO_PULLDOWN
PC7.Signal=GPIO_Input
PC8.GPIOParameters=GPIO_PuPd,GPIO_Label
PC8.GPIO_Label=P2_DATA_0
PC8.GPIO_PuPd=GPIO_PULLDOWN
PC8.Signal=GPIO_Input
PC9.GPIOParameters=GPIO_PuPd,GPIO_Label
PC9.GPIO_Label=P2_DATA_2
PC9.GPIO_PuPd=GPIO_PULLDOWN
PC9.Signal=GPIO_Input
PD2.GPIOParameters=GPIO_Label
PD2.GPIO_Label=V2_DATA_3
PD2.Signal=GPIO_Output
PH0-OSC_IN.Mode=HSE-External-Oscillator
PH0-OSC_IN.Signal=RCC_OSC_IN
PH1-OSC_OUT.Mode=HSE-External-Oscillator
PH1-OSC_OUT.Signal=RCC_OSC_OUT
RCC.HSE_VALUE=8000000
RCC.SYSCLKFreq_VALUE=168000000
RCC.SYSCLKSource=RCC_SYSCLKSOURCE_PLLCLK
board=NUCLEO-F446RE
boardIOC=true

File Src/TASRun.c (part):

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
	// tristate all external buffers on v4 board (i.e. set their enable pins high)
	#ifdef BOARDV4
	SetupPin(ENABLE_D0D1_GPIO_Port, ENABLE_D0D1_Pin, GPIO_MODE_OUTPUT_PP, GPIO_NOPULL, GPIO_PIN_SET);
	SetupPin(ENABLE_P1D2D3_GPIO_Port, ENABLE_P1D2D3_Pin, GPIO_MODE_OUTPUT_PP, GPIO_NOPULL, GPIO_PIN_SET);
	SetupPin(ENABLE_P2D2D3_GPIO_Port, ENABLE_P2D2D3_Pin, GPIO_MODE_OUTPUT_PP, GPIO_NOPULL, GPIO_PIN_SET);
	#endif

	// Switches, input pullup (just to be explicit)
	SetupPin(SWITCH1_GPIO_Port, SWITCH1_Pin, GPIO_MODE_INPUT, GPIO_PULLUP, GPIO_PIN_SET);
	SetupPin(SWITCH2_GPIO_Port, SWITCH2_Pin, GPIO_MODE_INPUT, GPIO_PULLUP, GPIO_PIN_SET);
	SetupPin(SWITCH3_GPIO_Port, SWITCH3_Pin, GPIO_MODE_INPUT, GPIO_PULLUP, GPIO_PIN_SET);
	SetupPin(SWITCH4_GPIO_Port, SWITCH4_Pin, GPIO_MODE_INPUT, GPIO_PULLUP, GPIO_PIN_SET);

	/*Configure Visualization pins: V1_CLOCK_Pin V1_LATCH_Pin V1_DATA_1_Pin V1_DATA_0_Pin */
	SetupPin(V1_DATA_0_GPIO_Port, V1_CLOCK_Pin|V1_LATCH_Pin|V1_DATA_1_Pin|V1_DATA_0_Pin, GPIO_MODE_OUTPUT_PP, GPIO_NOPULL, GPIO_PIN_RESET);

	/*Configure Visualization pins: V2_CLOCK_Pin V2_LATCH_Pin V2_DATA_1_Pin V2_DATA_0_Pin */
	SetupPin(V2_DATA_0_GPIO_Port, V2_LATCH_Pin|V2_DATA_1_Pin|V2_DATA_0_Pin, GPIO_MODE_OUTPUT_PP, GPIO_NOPULL, GPIO_PIN_RESET);
	SetupPin(V2_CLOCK_GPIO_Port, V2_CLOCK_Pin, GPIO_MODE_OUTPUT_PP, GPIO_NOPULL, GPIO_PIN_RESET);

	/*Configure Console Reset pin: */
	SetupPin(SNES_RESET_GPIO_Port, SNES_RESET_Pin, GPIO_MODE_OUTPUT_OD, GPIO_NOPULL, GPIO_PIN_SET);

	/* EXTI interrupt init*/
	HAL_NVIC_SetPriority(EXTI0_IRQn, 0, 0);
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	// clear all interrupts
	while (HAL_NVIC_GetPendingIRQ(EXTI0_IRQn))
	{
		__HAL_GPIO_EXTI_CLEAR_IT(P1_CLOCK_Pin);
		HAL_NVIC_ClearPendingIRQ(EXTI0_IRQn);
	}
	while (HAL_NVIC_GetPendingIRQ(EXTI1_IRQn))
	{
		__HAL_GPIO_EXTI_CLEAR_IT(P1_LATCH_Pin);
		HAL_NVIC_ClearPendingIRQ(EXTI1_IRQn);
	}
	while (HAL_NVIC_GetPendingIRQ(EXTI4_IRQn))
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	}
	while (HAL_NVIC_GetPendingIRQ(EXTI9_5_IRQn))
	{
		__HAL_GPIO_EXTI_CLEAR_IT(P2_CLOCK_Pin);
		__HAL_GPIO_EXTI_CLEAR_IT(P2_DATA_2_Pin);
		HAL_NVIC_ClearPendingIRQ(EXTI9_5_IRQn);
	}
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	#ifdef BOARDV4
	// external output buffers should already be tristated, so set direction to output (i.e. high)
	// Buffer will be enabled on first latch
	SetupPin(DIR_D0D1_GPIO_Port, DIR_D0D1_Pin, GPIO_MODE_OUTPUT_PP, GPIO_NOPULL, GPIO_PIN_SET);
	SetupPin(DIR_P1D2D3_GPIO_Port, DIR_P1D2D3_Pin, GPIO_MODE_OUTPUT_PP, GPIO_NOPULL, GPIO_PIN_SET);
	SetupPin(DIR_P2D2D3_GPIO_Port, DIR_P2D2D3_Pin, GPIO_MODE_OUTPUT_PP, GPIO_NOPULL, GPIO_PIN_SET);

	// Now do the actual MCU pins
	// MCU D0/D1/D2/D3 output, but they will not actually speak to console yet as buffer is disabled
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	#endif //BOARDV4

	// MCU Clock/latch input, triggered on rising edge
	SetupPin(GPIOC, P1_CLOCK_Pin|P1_LATCH_Pin|P2_CLOCK_Pin, GPIO_MODE_IT_RISING, GPIO_NOPULL, GPIO_PIN_RESET);

	// Ensure the proper callback function is used for pin 1
	volatile uint32_t* ptr = (void *)(SRAM_BASE + 0x40 + (EXTI1_IRQn * 4));
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
	// external output buffers should already be tristated, so set direction to output (i.e. high)
	// Buffer will be enabled on first latch
	SetupPin(DIR_D0D1_GPIO_Port, DIR_D0D1_Pin, GPIO_MODE_OUTPUT_PP, GPIO_NOPULL, GPIO_PIN_SET);
	SetupPin(DIR_P1D2D3_GPIO_Port, DIR_P1D2D3_Pin, GPIO_MODE_OUTPUT_PP, GPIO_NOPULL, GPIO_PIN_SET);
	SetupPin(DIR_P2D2D3_GPIO_Port, DIR_P2D2D3_Pin, GPIO_MODE_OUTPUT_PP, GPIO_NOPULL, GPIO_PIN_SET);

	// Now do the actual MCU pins
	// MCU D0/D1 output, but they will not actually speak to console yet as buffer is disabled
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	#endif //BOARDV4

	// MCU Clock/latch input, triggered on rising edge
	SetupPin(GPIOC, P1_CLOCK_Pin|P1_LATCH_Pin|P2_CLOCK_Pin, GPIO_MODE_IT_RISING, GPIO_NOPULL, GPIO_PIN_RESET);

	// Ensure the proper callback function is used for pin 1
	volatile uint32_t* ptr = (void *)(SRAM_BASE + 0x40 + (EXTI1_IRQn * 4));
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
void SetGENMode()
{
	// P1_D0 --> GEN Pin 1
	// P1_D1 --> GEN Pin 2
	// P1_D2 --> GEN Pin 3
	// P2_D0 --> GEN Pin 4
	// P2_D1 --> GEN Pin 6
	// P2_D2 --> GEN Pin 9
	#ifdef BOARDV3

	// MCU D0/D1/D2 input for now, will be made output on first latch
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	
	// Latch pin only interrupts on falling to avoid triggering when console powers on
	// will be set to rising-falling after first interrupt
	SetupPin(P1_LATCH_GPIO_Port, P1_LATCH_Pin, GPIO_MODE_IT_FALLING, GPIO_PULLUP, GPIO_PIN_RESET);
	#endif

	#ifdef BOARDV4

	// external output buffers should already be tristated, so set direction to output (i.e. high)
	// Buffer will be enabled on first latch
	SetupPin(DIR_D0D1_GPIO_Port, DIR_D0D1_Pin, GPIO_MODE_OUTPUT_PP, GPIO_NOPULL, GPIO_PIN_SET);
	SetupPin(DIR_P1D2D3_GPIO_Port, DIR_P1D2D3_Pin, GPIO_MODE_OUTPUT_PP, GPIO_NOPULL, GPIO_PIN_SET);
	SetupPin(DIR_P2D2D3_GPIO_Port, DIR_P2D2D3_Pin, GPIO_MODE_OUTPUT_PP, GPIO_NOPULL, GPIO_PIN_SET);

	// MCU D0/D1/D2/D3 output, but they will not actually speak to console yet as buffer is disabled
	SetupPin(P1_DATA_0_GPIO_Port, P1_DATA_0_Pin, GPIO_MODE_OUTPUT_PP, GPIO_NOPULL, GPIO_PIN_SET);
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	
	// Latch pin only interrupts on falling to avoid triggering when console powers on
	// will be set to rising-falling after first interrupt
	SetupPin(P1_LATCH_GPIO_Port, P1_LATCH_Pin, GPIO_MODE_IT_FALLING, GPIO_NOPULL, GPIO_PIN_RESET);

	#endif

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

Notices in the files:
parts and their libraries:
SparkFun-Connectors: Licensing: Creative Commons ShareAlike 4.0 International - https://creativecommons.org/licenses/by-sa/4.0
